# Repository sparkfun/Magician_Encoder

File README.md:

Magician Chassis Encoder
==================

Reflectance based wheel encoder for use with the Magician chassis; supported by the RedBot Library.

[  
*Magician Chassis Encoder*](https://www.sparkfun.com/products/12617)

Design files and firmware files for the [Magician Chassis Encoder](https://www.sparkfun.com/products/12617).

Repository Contents
-------------------

* **/hardware** - Eagle PCB layout files
* **/Production Files** - Files to support SparkFun production

License Information
-------------------

All contents of this repository are released under [Creative Commons Share-alike 3.0](http://creativecommons.org/licenses/by-sa/3.0/).

Authors: Mike Hord @ SparkFun Electonics

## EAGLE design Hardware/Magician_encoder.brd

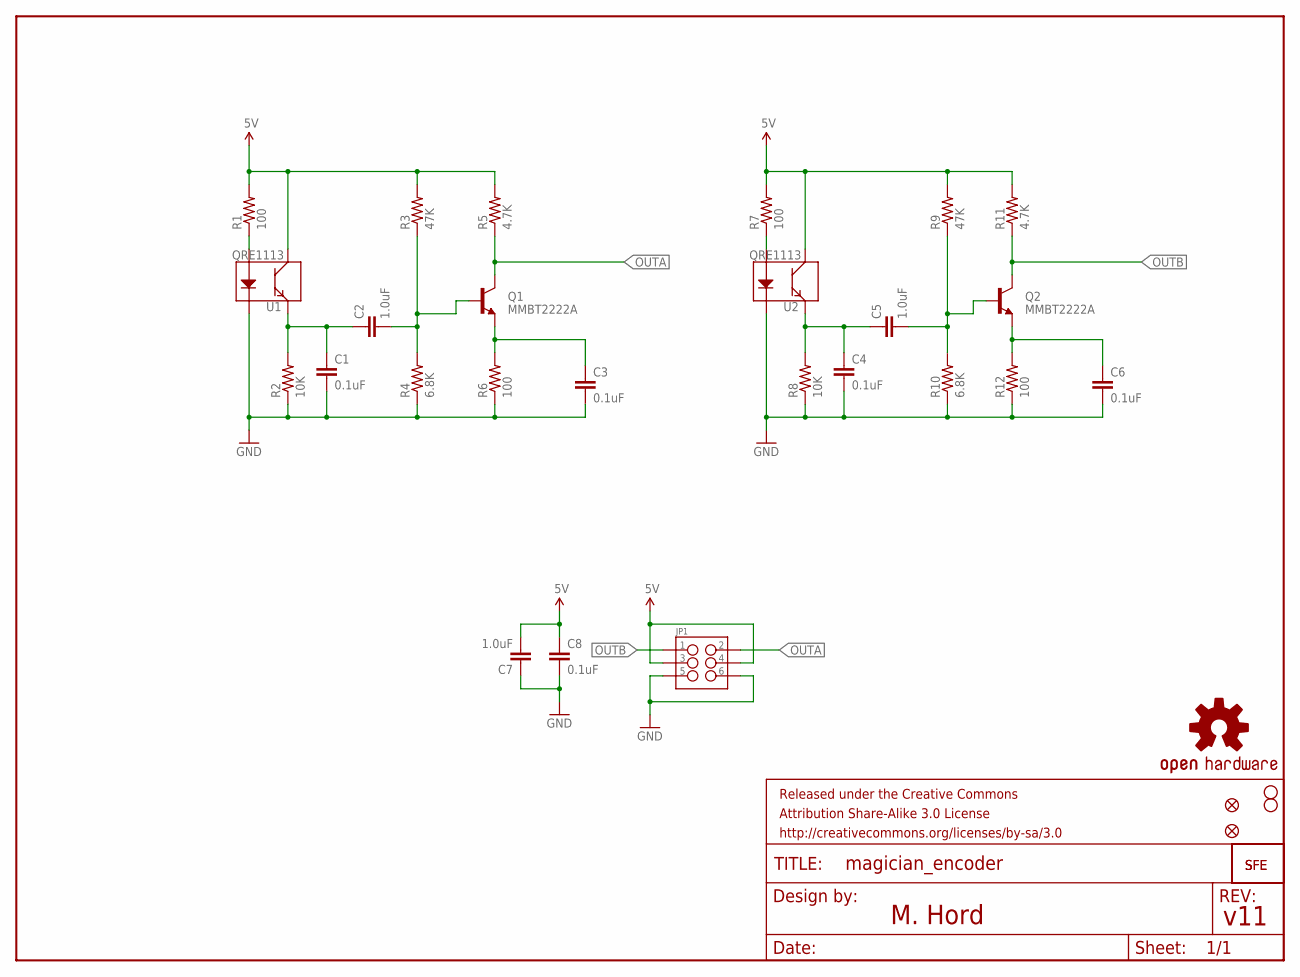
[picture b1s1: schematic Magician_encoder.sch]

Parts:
C1, C3, C4, C6, C8: 0.1uF; 0603-CAP
C2, C5, C7: 1.0uF; 0603-CAP
FID1, FID2: FIDUCIALUFIDUCIAL; MICRO-FIDUCIAL
FRAME1: FRAME-LETTER; CREATIVE_COMMONS
JP1: M03X2SMT; 2X3_SMT_POSTS
LOGO1: LOGO-SFESK; SFE-LOGO-FLAME
LOGO3: OSHW-LOGOS; OSHW-LOGO-S
LOGO4: LOGO-SFENEW; SFE-NEW-WEBLOGO
Q1, Q2: MMBT2222A; SOT23
R1, R6, R7, R12: 100; 0603-RES
R2, R8: 10K; 0603-RES
R3, R9: 47K; 0603-RES
R4, R10: 6.8K; 0603-RES
R5, R11: 4.7K; 0603-RES
STANDOFF1, STANDOFF2: STAND-OFF
U1, U2: QRE1113

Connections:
5V: C7.2, C8.1, JP1.3, JP1.4, R1.2, R3.2, R5.2, R7.2, R9.2, R11.2, U1.3 (C), U2.3 (C)
GND: C1.2, C3.2, C4.2, C6.2, C7.1, C8.2, JP1.5, JP1.6, R2.1, R4.1, R6.1, R8.1, R10.1, R12.1, U1.2 (K), U2.2 (K)
unnamed: C1.1, C2.1, R2.2, U1.4 (E)
unnamed: C2.2, Q1.1 (B), R3.1, R4.2
unnamed: C3.1, Q1.2 (E), R6.2
unnamed: R1.1, U1.1 (A)
unnamed: C6.1, Q2.2 (E), R12.2
unnamed: C4.1, C5.1, R8.2, U2.4 (E)
unnamed: C5.2, Q2.1 (B), R9.1, R10.2
unnamed: R7.1, U2.1 (A)
OUTA: JP1.2, Q1.3 (C), R5.1
OUTB: JP1.1, Q2.3 (C), R11.1

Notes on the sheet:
v11
M. Hord

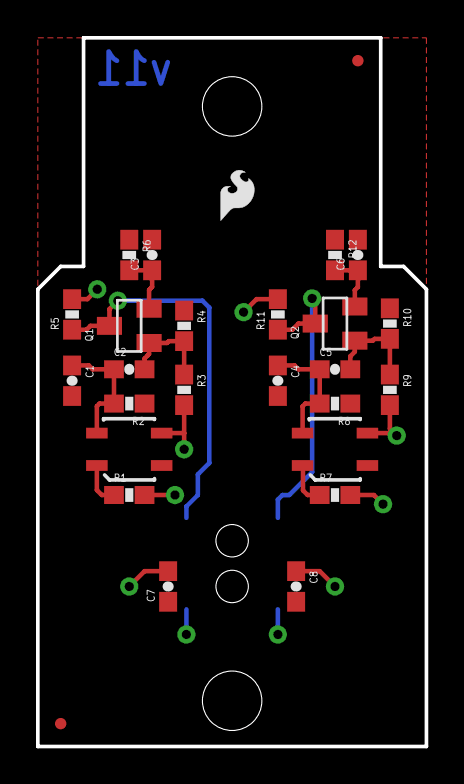
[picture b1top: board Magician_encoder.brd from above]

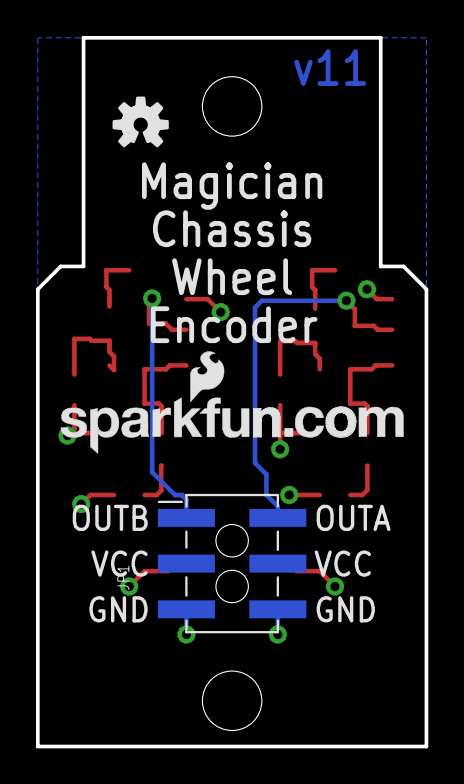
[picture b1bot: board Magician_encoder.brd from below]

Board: 2 copper layers, 21.6 x 39.4 mm, 33 parts (3 on the bottom side), 12 nets.

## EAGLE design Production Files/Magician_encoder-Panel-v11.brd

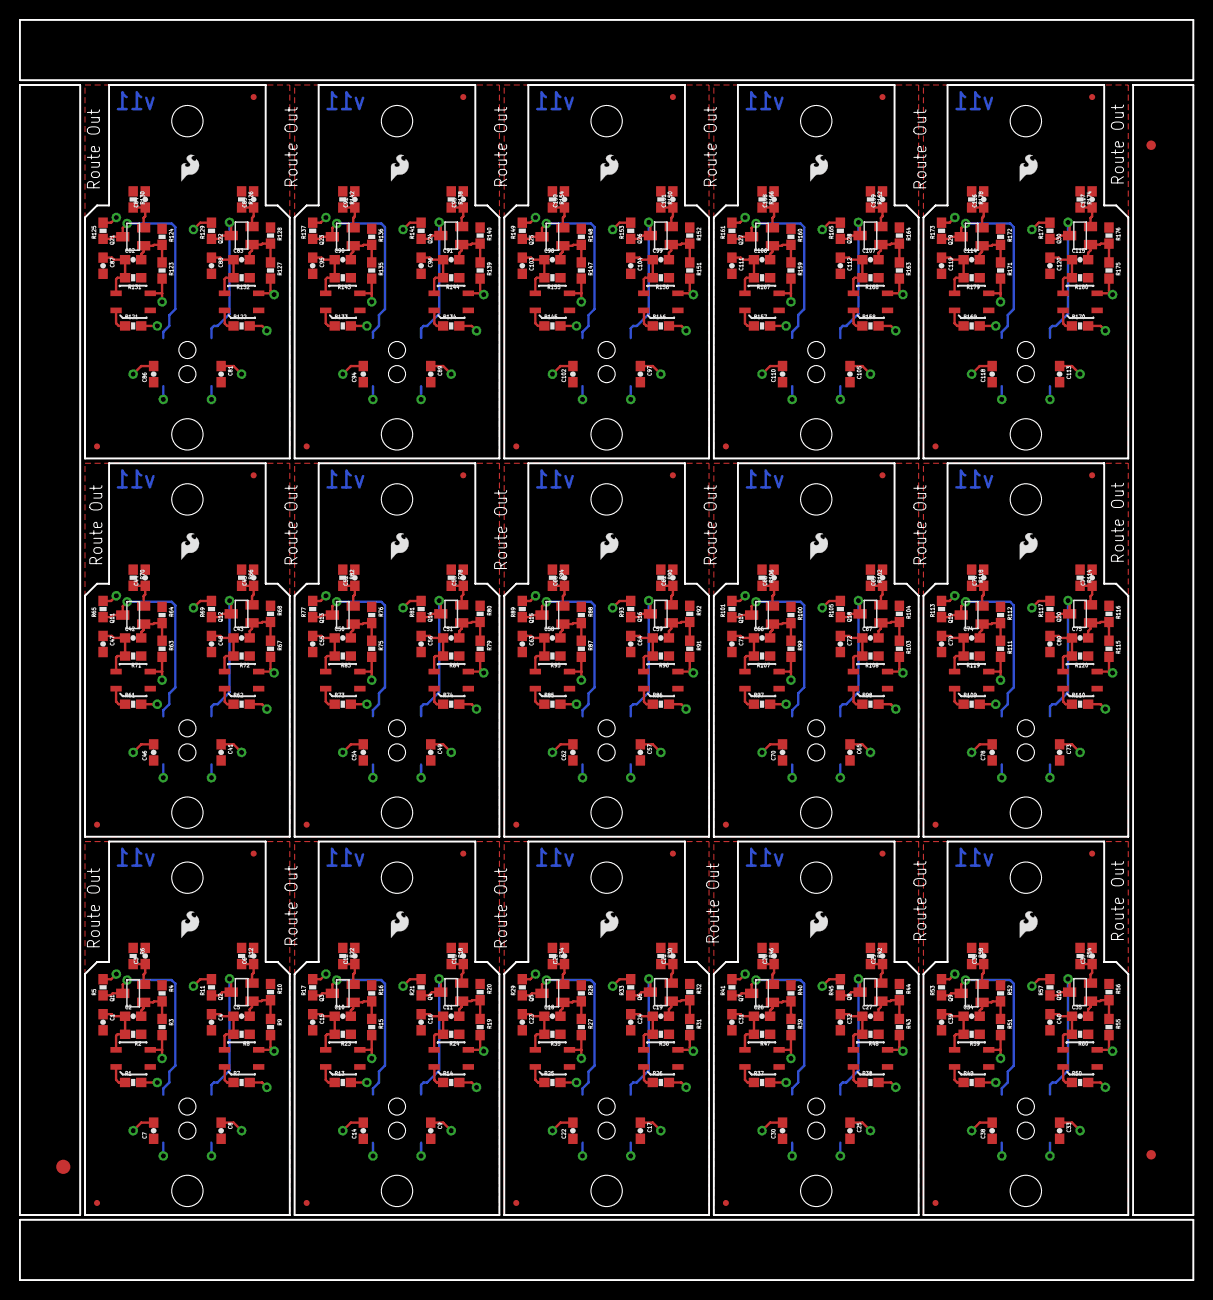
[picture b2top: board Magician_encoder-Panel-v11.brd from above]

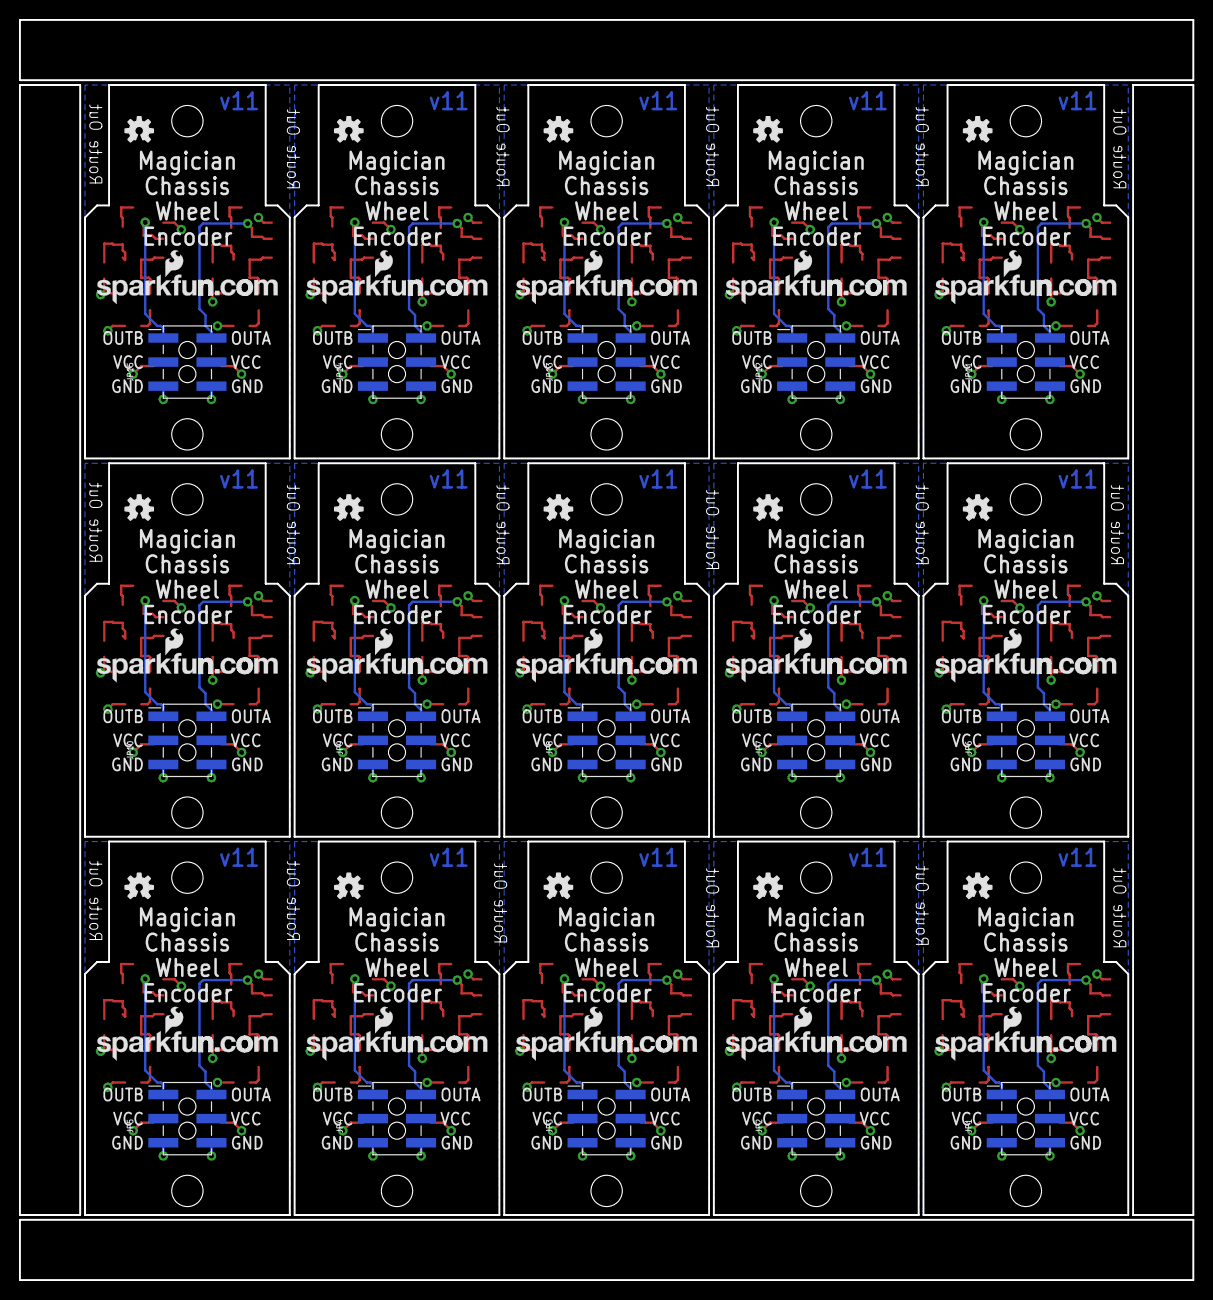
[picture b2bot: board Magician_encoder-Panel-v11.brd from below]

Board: 2 copper layers, 123.7 x 132.8 mm, 483 parts (45 on the bottom side), 180 nets.

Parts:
C1, C3, C4, C6, C8, C9, C12, C13, C15, C16, C17, C20, C21, C23, C24, C25, C28, C29, C31, C32, C33, C36, C37, C39, C40, C41, C44, C45, C47, C48, C49, C52, C53, C55, C56, C57, C60, C61, C63, C64, C65, C68, C69, C71, C72, C73, C76, C77, C79, C80, C81, C84, C85, C87, C88, C89, C92, C93, C95, C96, C97, C100, C101, C103, C104, C105, C108, C109, C111, C112, C113, C116, C117, C119, C120: 0.1uF; 0603-CAP
C2, C5, C7, C10, C11, C14, C18, C19, C22, C26, C27, C30, C34, C35, C38, C42, C43, C46, C50, C51, C54, C58, C59, C62, C66, C67, C70, C74, C75, C78, C82, C83, C86, C90, C91, C94, C98, C99, C102, C106, C107, C110, C114, C115, C118: 1.0uF; 0603-CAP
E$1: FIDUCIAL-1.5X3
E$4, E$5: FIDUCIAL-1X2
FID1, FID2, FID3, FID4, FID5, FID6, FID7, FID8, FID9, FID10, FID11, FID12, FID13, FID14, FID15, FID16, FID17, FID18, FID19, FID20, FID21, FID22, FID23, FID24, FID25, FID26, FID27, FID28, FID29, FID30: FIDUCIALUFIDUCIAL; MICRO-FIDUCIAL
JP1, JP2, JP3, JP4, JP5, JP6, JP7, JP8, JP9, JP10, JP11, JP12, JP13, JP14, JP15: 2X3_SMT_POSTS
LOGO1, LOGO6, LOGO9, LOGO12, LOGO15, LOGO18, LOGO21, LOGO24, LOGO27, LOGO30, LOGO33, LOGO36, LOGO39, LOGO42, LOGO45: LOGO-SFESK; SFE-LOGO-FLAME
LOGO2, LOGO3, LOGO7, LOGO10, LOGO13, LOGO16, LOGO19, LOGO22, LOGO25, LOGO28, LOGO31, LOGO34, LOGO37, LOGO40, LOGO43: OSHW-LOGOS; OSHW-LOGO-S
LOGO4, LOGO5, LOGO8, LOGO11, LOGO14, LOGO17, LOGO20, LOGO23, LOGO26, LOGO29, LOGO32, LOGO35, LOGO38, LOGO41, LOGO44: LOGO-SFENEW; SFE-NEW-WEBLOGO
Q1, Q2, Q3, Q4, Q5, Q6, Q7, Q8, Q9, Q10, Q11, Q12, Q13, Q14, Q15, Q16, Q17, Q18, Q19, Q20, Q21, Q22, Q23, Q24, Q25, Q26, Q27, Q28, Q29, Q30: MMBT2222A; SOT23
R1, R6, R7, R12, R13, R14, R18, R22, R25, R26, R30, R34, R37, R38, R42, R46, R49, R50, R54, R58, R61, R62, R66, R70, R73, R74, R78, R82, R85, R86, R90, R94, R97, R98, R102, R106, R109, R110, R114, R118, R121, R122, R126, R130, R133, R134, R138, R142, R145, R146, R150, R154, R157, R158, R162, R166, R169, R170, R174, R178: 100; 0603-RES
R2, R8, R23, R24, R35, R36, R47, R48, R59, R60, R71, R72, R83, R84, R95, R96, R107, R108, R119, R120, R131, R132, R143, R144, R155, R156, R167, R168, R179, R180: 10K; 0603-RES
R3, R9, R15, R19, R27, R31, R39, R43, R51, R55, R63, R67, R75, R79, R87, R91, R99, R103, R111, R115, R123, R127, R135, R139, R147, R151, R159, R163, R171, R175: 47K; 0603-RES
R4, R10, R16, R20, R28, R32, R40, R44, R52, R56, R64, R68, R76, R80, R88, R92, R100, R104, R112, R116, R124, R128, R136, R140, R148, R152, R160, R164, R172, R176: 6.8K; 0603-RES
R5, R11, R17, R21, R29, R33, R41, R45, R53, R57, R65, R69, R77, R81, R89, R93, R101, R105, R113, R117, R125, R129, R137, R141, R149, R153, R161, R165, R173, R177: 4.7K; 0603-RES
STANDOFF1, STANDOFF2, STANDOFF3, STANDOFF4, STANDOFF5, STANDOFF6, STANDOFF7, STANDOFF8, STANDOFF9, STANDOFF10, STANDOFF11, STANDOFF12, STANDOFF13, STANDOFF14, STANDOFF15, STANDOFF16, STANDOFF17, STANDOFF18, STANDOFF19, STANDOFF20, STANDOFF21, STANDOFF22, STANDOFF23, STANDOFF24, STANDOFF25, STANDOFF26, STANDOFF27, STANDOFF28, STANDOFF29, STANDOFF30: STAND-OFF
U1, U2, U3, U4, U5, U6, U7, U8, U9, U10, U11, U12, U13, U14, U15, U16, U17, U18, U19, U20, U21, U22, U23, U24, U25, U26, U27, U28, U29, U30: QRE1113

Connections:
5V: C7.2, C8.1, JP1.3, JP1.4, R1.2, R3.2, R5.2, R7.2, R9.2, R11.2, U1.3, U2.3
5V1: C9.1, C14.2, JP2.3, JP2.4, R13.2, R14.2, R15.2, R17.2, R19.2, R21.2, U3.3, U4.3
5V2: C17.1, C22.2, JP3.3, JP3.4, R25.2, R26.2, R27.2, R29.2, R31.2, R33.2, U5.3, U6.3
5V3: C25.1, C30.2, JP4.3, JP4.4, R37.2, R38.2, R39.2, R41.2, R43.2, R45.2, U7.3, U8.3
5V4: C33.1, C38.2, JP5.3, JP5.4, R49.2, R50.2, R51.2, R53.2, R55.2, R57.2, U9.3, U10.3
5V5: C41.1, C46.2, JP6.3, JP6.4, R61.2, R62.2, R63.2, R65.2, R67.2, R69.2, U11.3, U12.3
5V6: C49.1, C54.2, JP7.3, JP7.4, R73.2, R74.2, R75.2, R77.2, R79.2, R81.2, U13.3, U14.3
5V7: C57.1, C62.2, JP8.3, JP8.4, R85.2, R86.2, R87.2, R89.2, R91.2, R93.2, U15.3, U16.3
5V8: C65.1, C70.2, JP9.3, JP9.4, R97.2, R98.2, R99.2, R101.2, R103.2, R105.2, U17.3, U18.3
5V9: C73.1, C78.2, JP10.3, JP10.4, R109.2, R110.2, R111.2, R113.2, R115.2, R117.2, U19.3, U20.3
5V10: C81.1, C86.2, JP11.3, JP11.4, R121.2, R122.2, R123.2, R125.2, R127.2, R129.2, U21.3, U22.3
5V11: C89.1, C94.2, JP12.3, JP12.4, R133.2, R134.2, R135.2, R137.2, R139.2, R141.2, U23.3, U24.3
5V12: C97.1, C102.2, JP13.3, JP13.4, R145.2, R146.2, R147.2, R149.2, R151.2, R153.2, U25.3, U26.3
5V13: C105.1, C110.2, JP14.3, JP14.4, R157.2, R158.2, R159.2, R161.2, R163.2, R165.2, U27.3, U28.3
5V14: C113.1, C118.2, JP15.3, JP15.4, R169.2, R170.2, R171.2, R173.2, R175.2, R177.2, U29.3, U30.3
GND: C1.2, C3.2, C4.2, C6.2, C7.1, C8.2, JP1.5, JP1.6, R2.1, R4.1, R6.1, R8.1, R10.1, R12.1, U1.2, U2.2
GND1: C9.2, C12.2, C13.2, C14.1, C15.2, C16.2, JP2.5, JP2.6, R16.1, R18.1, R20.1, R22.1, R23.1, R24.1, U3.2, U4.2
GND2: C17.2, C20.2, C21.2, C22.1, C23.2, C24.2, JP3.5, JP3.6, R28.1, R30.1, R32.1, R34.1, R35.1, R36.1, U5.2, U6.2
GND3: C25.2, C28.2, C29.2, C30.1, C31.2, C32.2, JP4.5, JP4.6, R40.1, R42.1, R44.1, R46.1, R47.1, R48.1, U7.2, U8.2
GND4: C33.2, C36.2, C37.2, C38.1, C39.2, C40.2, JP5.5, JP5.6, R52.1, R54.1, R56.1, R58.1, R59.1, R60.1, U9.2, U10.2
GND5: C41.2, C44.2, C45.2, C46.1, C47.2, C48.2, JP6.5, JP6.6, R64.1, R66.1, R68.1, R70.1, R71.1, R72.1, U11.2, U12.2
GND6: C49.2, C52.2, C53.2, C54.1, C55.2, C56.2, JP7.5, JP7.6, R76.1, R78.1, R80.1, R82.1, R83.1, R84.1, U13.2, U14.2
GND7: C57.2, C60.2, C61.2, C62.1, C63.2, C64.2, JP8.5, JP8.6, R88.1, R90.1, R92.1, R94.1, R95.1, R96.1, U15.2, U16.2
GND8: C65.2, C68.2, C69.2, C70.1, C71.2, C72.2, JP9.5, JP9.6, R100.1, R102.1, R104.1, R106.1, R107.1, R108.1, U17.2, U18.2
GND9: C73.2, C76.2, C77.2, C78.1, C79.2, C80.2, JP10.5, JP10.6, R112.1, R114.1, R116.1, R118.1, R119.1, R120.1, U19.2, U20.2
GND10: C81.2, C84.2, C85.2, C86.1, C87.2, C88.2, JP11.5, JP11.6, R124.1, R126.1, R128.1, R130.1, R131.1, R132.1, U21.2, U22.2
GND11: C89.2, C92.2, C93.2, C94.1, C95.2, C96.2, JP12.5, JP12.6, R136.1, R138.1, R140.1, R142.1, R143.1, R144.1, U23.2, U24.2
GND12: C97.2, C100.2, C101.2, C102.1, C103.2, C104.2, JP13.5, JP13.6, R148.1, R150.1, R152.1, R154.1, R155.1, R156.1, U25.2, U26.2
GND13: C105.2, C108.2, C109.2, C110.1, C111.2, C112.2, JP14.5, JP14.6, R160.1, R162.1, R164.1, R166.1, R167.1, R168.1, U27.2, U28.2
GND14: C113.2, C116.2, C117.2, C118.1, C119.2, C120.2, JP15.5, JP15.6, R172.1, R174.1, R176.1, R178.1, R179.1, R180.1, U29.2, U30.2
unnamed: C1.1, C2.1, R2.2, U1.4
unnamed: C2.2, Q1.1, R3.1, R4.2
unnamed: C3.1, Q1.2, R6.2
unnamed: R13.1, U3.1
unnamed: R1.1, U1.1
unnamed: R14.1, U4.1
unnamed: C6.1, Q2.2, R12.2
unnamed: C4.1, C5.1, R8.2, U2.4
unnamed: C5.2, Q2.1, R9.1, R10.2
unnamed: R7.1, U2.1
unnamed: C10.1, C15.1, R23.2, U3.4
unnamed: C10.2, Q3.1, R15.1, R16.2
unnamed: C12.1, Q3.2, R22.2
unnamed: C13.1, Q4.2, R18.2
unnamed: C11.1, C16.1, R24.2, U4.4
unnamed: C11.2, Q4.1, R19.1, R20.2
unnamed: R25.1, U5.1
unnamed: R26.1, U6.1
unnamed: C18.1, C23.1, R35.2, U5.4
unnamed: C18.2, Q5.1, R27.1, R28.2
unnamed: C20.1, Q5.2, R34.2
unnamed: C21.1, Q6.2, R30.2
unnamed: C19.1, C24.1, R36.2, U6.4
unnamed: C19.2, Q6.1, R31.1, R32.2
unnamed: R37.1, U7.1
unnamed: R38.1, U8.1
unnamed: C26.1, C31.1, R47.2, U7.4
unnamed: C26.2, Q7.1, R39.1, R40.2
unnamed: C28.1, Q7.2, R46.2
unnamed: C29.1, Q8.2, R42.2
unnamed: C27.1, C32.1, R48.2, U8.4
unnamed: C27.2, Q8.1, R43.1, R44.2
unnamed: R49.1, U9.1
unnamed: R50.1, U10.1
unnamed: C34.1, C39.1, R59.2, U9.4
unnamed: C34.2, Q9.1, R51.1, R52.2
unnamed: C36.1, Q9.2, R58.2
unnamed: C37.1, Q10.2, R54.2
unnamed: C35.1, C40.1, R60.2, U10.4
unnamed: C35.2, Q10.1, R55.1, R56.2
unnamed: R61.1, U11.1
unnamed: R62.1, U12.1
unnamed: C42.1, C47.1, R71.2, U11.4
unnamed: C42.2, Q11.1, R63.1, R64.2
unnamed: C44.1, Q11.2, R70.2
unnamed: C45.1, Q12.2, R66.2
unnamed: C43.1, C48.1, R72.2, U12.4
unnamed: C43.2, Q12.1, R67.1, R68.2
unnamed: R73.1, U13.1
unnamed: R74.1, U14.1
unnamed: C50.1, C55.1, R83.2, U13.4
unnamed: C50.2, Q13.1, R75.1, R76.2
unnamed: C52.1, Q13.2, R82.2
unnamed: C53.1, Q14.2, R78.2
unnamed: C51.1, C56.1, R84.2, U14.4
unnamed: C51.2, Q14.1, R79.1, R80.2
unnamed: R85.1, U15.1
unnamed: R86.1, U16.1
unnamed: C58.1, C63.1, R95.2, U15.4
unnamed: C58.2, Q15.1, R87.1, R88.2
unnamed: C60.1, Q15.2, R94.2
unnamed: C61.1, Q16.2, R90.2
unnamed: C59.1, C64.1, R96.2, U16.4
unnamed: C59.2, Q16.1, R91.1, R92.2
unnamed: R97.1, U17.1
unnamed: R98.1, U18.1
unnamed: C66.1, C71.1, R107.2, U17.4
unnamed: C66.2, Q17.1, R99.1, R100.2
unnamed: C68.1, Q17.2, R106.2
unnamed: C69.1, Q18.2, R102.2
unnamed: C67.1, C72.1, R108.2, U18.4
unnamed: C67.2, Q18.1, R103.1, R104.2
unnamed: R109.1, U19.1
unnamed: R110.1, U20.1
unnamed: C74.1, C79.1, R119.2, U19.4
unnamed: C74.2, Q19.1, R111.1, R112.2
unnamed: C76.1, Q19.2, R118.2
unnamed: C77.1, Q20.2, R114.2
unnamed: C75.1, C80.1, R120.2, U20.4
unnamed: C75.2, Q20.1, R115.1, R116.2
unnamed: R121.1, U21.1
unnamed: R122.1, U22.1
unnamed: C82.1, C87.1, R131.2, U21.4
unnamed: C82.2, Q21.1, R123.1, R124.2
unnamed: C84.1, Q21.2, R130.2
unnamed: C85.1, Q22.2, R126.2
unnamed: C83.1, C88.1, R132.2, U22.4
unnamed: C83.2, Q22.1, R127.1, R128.2
unnamed: R133.1, U23.1
unnamed: R134.1, U24.1
unnamed: C90.1, C95.1, R143.2, U23.4
unnamed: C90.2, Q23.1, R135.1, R136.2
unnamed: C92.1, Q23.2, R142.2
unnamed: C93.1, Q24.2, R138.2
unnamed: C91.1, C96.1, R144.2, U24.4
unnamed: C91.2, Q24.1, R139.1, R140.2
unnamed: R145.1, U25.1
unnamed: R146.1, U26.1
unnamed: C98.1, C103.1, R155.2, U25.4
unnamed: C98.2, Q25.1, R147.1, R148.2
unnamed: C100.1, Q25.2, R154.2
unnamed: C101.1, Q26.2, R150.2
unnamed: C99.1, C104.1, R156.2, U26.4
unnamed: C99.2, Q26.1, R151.1, R152.2
unnamed: R157.1, U27.1
unnamed: R158.1, U28.1
unnamed: C106.1, C111.1, R167.2, U27.4
unnamed: C106.2, Q27.1, R159.1, R160.2
unnamed: C108.1, Q27.2, R166.2
unnamed: C109.1, Q28.2, R162.2
unnamed: C107.1, C112.1, R168.2, U28.4
unnamed: C107.2, Q28.1, R163.1, R164.2
unnamed: R169.1, U29.1
unnamed: R170.1, U30.1
unnamed: C114.1, C119.1, R179.2, U29.4
unnamed: C114.2, Q29.1, R171.1, R172.2
unnamed: C116.1, Q29.2, R178.2
unnamed: C117.1, Q30.2, R174.2
unnamed: C115.1, C120.1, R180.2, U30.4
unnamed: C115.2, Q30.1, R175.1, R176.2
OUTA: JP1.2, Q1.3, R5.1
OUTA1: JP2.2, Q3.3, R17.1
OUTA2: JP3.2, Q5.3, R29.1
OUTA3: JP4.2, Q7.3, R41.1
OUTA4: JP5.2, Q9.3, R53.1
OUTA5: JP6.2, Q11.3, R65.1
OUTA6: JP7.2, Q13.3, R77.1
OUTA7: JP8.2, Q15.3, R89.1
OUTA8: JP9.2, Q17.3, R101.1
OUTA9: JP10.2, Q19.3, R113.1
OUTA10: JP11.2, Q21.3, R125.1
OUTA11: JP12.2, Q23.3, R137.1
OUTA12: JP13.2, Q25.3, R149.1
OUTA13: JP14.2, Q27.3, R161.1
OUTA14: JP15.2, Q29.3, R173.1
OUTB: JP1.1, Q2.3, R11.1
OUTB1: JP2.1, Q4.3, R21.1
OUTB2: JP3.1, Q6.3, R33.1
OUTB3: JP4.1, Q8.3, R45.1
OUTB4: JP5.1, Q10.3, R57.1
OUTB5: JP6.1, Q12.3, R69.1
OUTB6: JP7.1, Q14.3, R81.1
OUTB7: JP8.1, Q16.3, R93.1
OUTB8: JP9.1, Q18.3, R105.1
OUTB9: JP10.1, Q20.3, R117.1
OUTB10: JP11.1, Q22.3, R129.1
OUTB11: JP12.1, Q24.3, R141.1
OUTB12: JP13.1, Q26.3, R153.1
OUTB13: JP14.1, Q28.3, R165.1
OUTB14: JP15.1, Q30.3, R177.1

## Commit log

2013-03-08 Initial commit, v01 files for protos.
2013-03-08 Changed opamp part number to U3
2013-05-28 Total overhaul to BJT based circuit.
2013-06-03 Change to discrete BJT circuit.
2013-08-14 Update values and circuit for better performance
2013-08-15 Production ready v10
    Fiducial addition and panel creation
2013-10-22 Update schematic with prod. values
2013-10-22 Put male SMT header on back
2013-11-26 Created Panel

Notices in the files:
parts and their libraries:
SparkFun-Aesthetics: Licensing: CC v3.0 Share-Alike You are welcome to use this library for commercial purposes.
SparkFun-Aesthetics: Released under the Creative Commons Attribution Share-Alike 3.0 License
SparkFun-Aesthetics: Released under the Creative Commons
